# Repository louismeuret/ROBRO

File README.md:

# ROBRO
To install toolchain, use sudo apt install gcc-arm-none-eabi binutils-arm-none-eabi libnewlib-arm-none-eabi
Then in the folder, write make

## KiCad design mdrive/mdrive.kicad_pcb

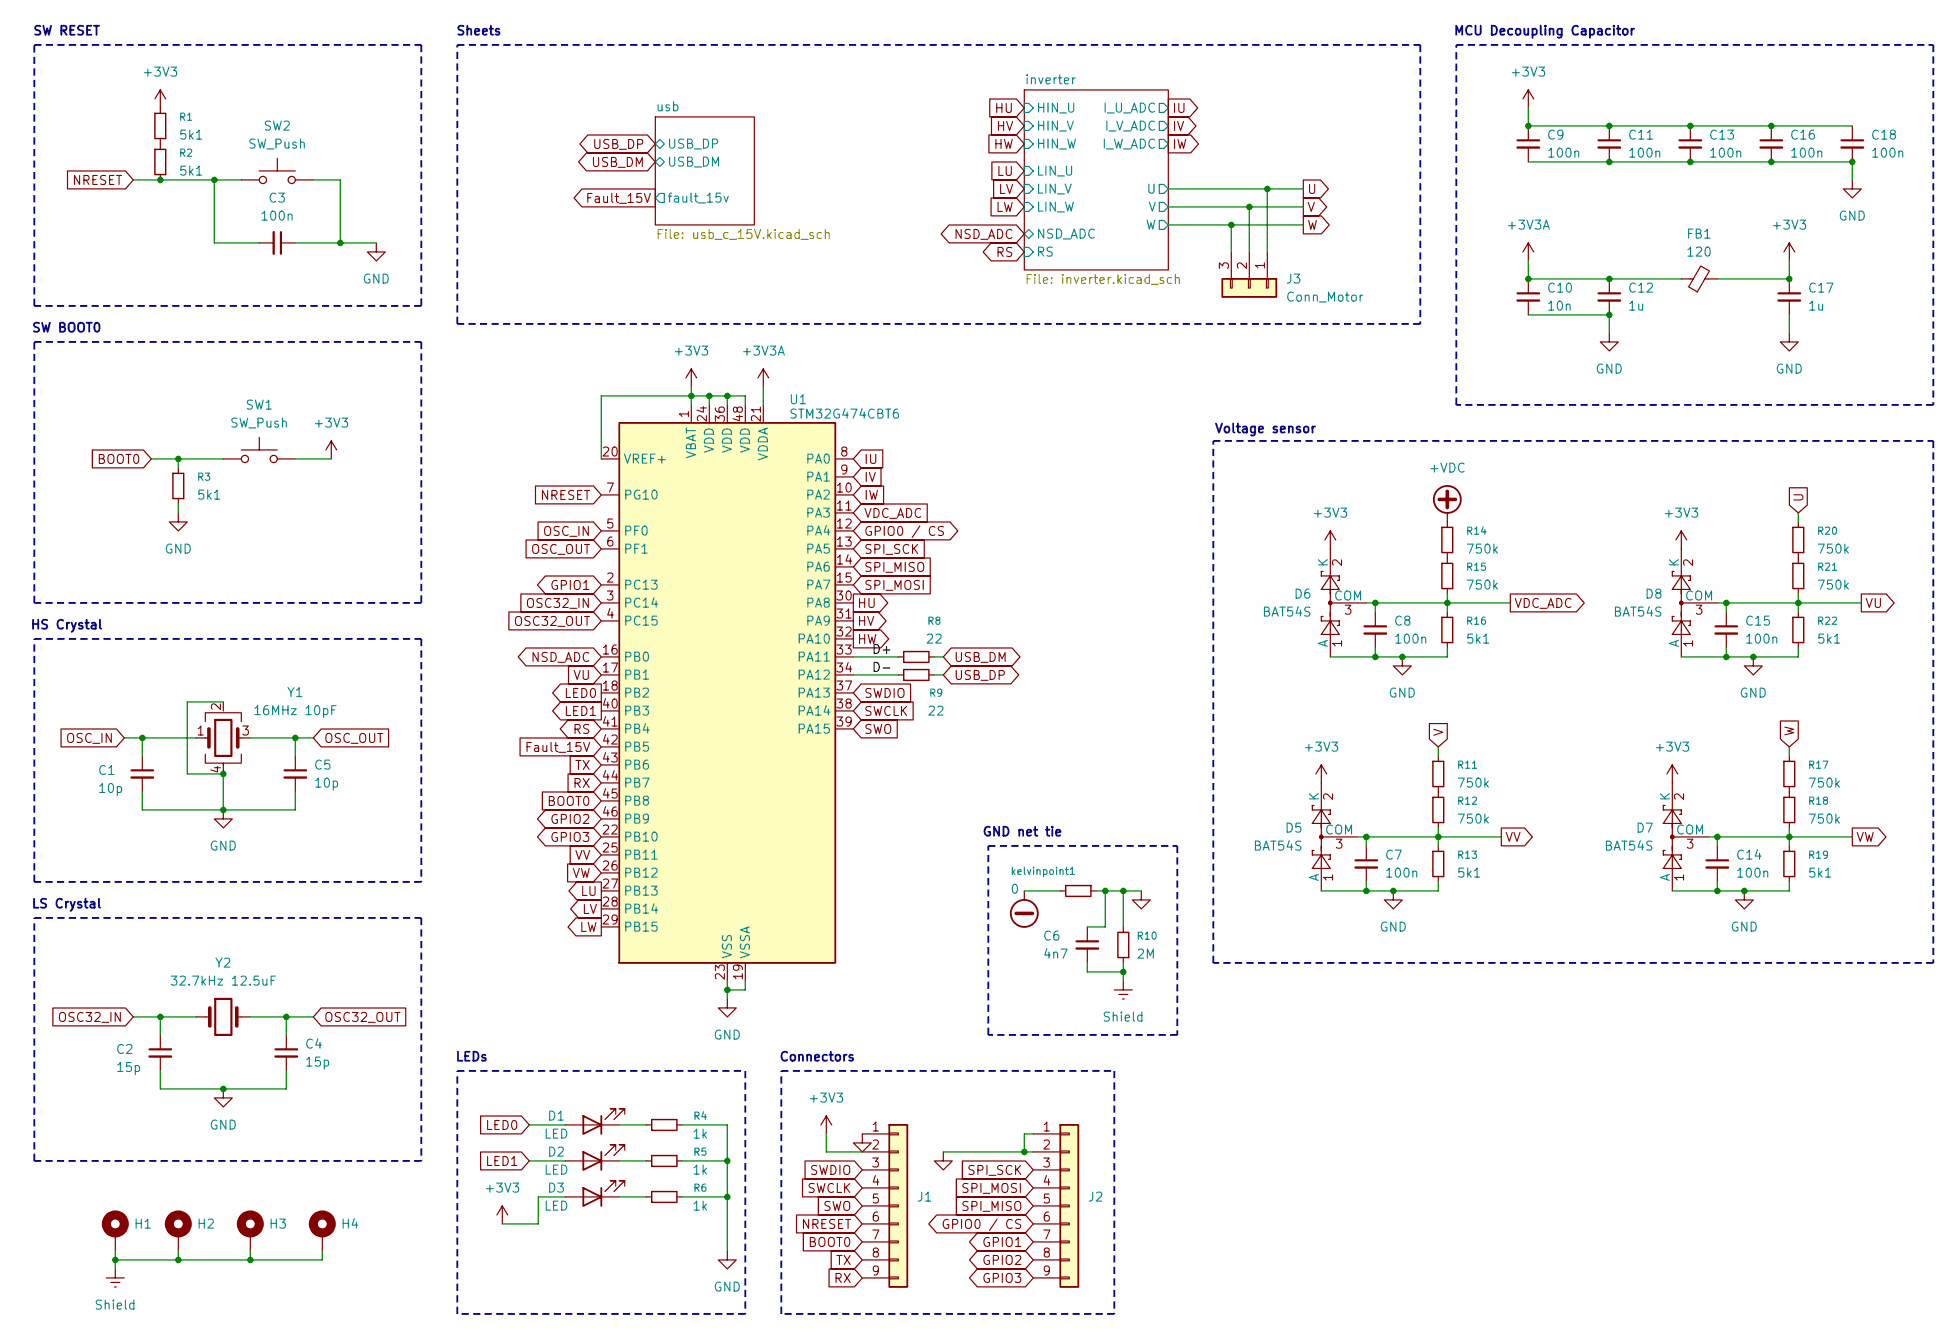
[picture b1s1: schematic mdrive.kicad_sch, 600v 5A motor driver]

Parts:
C1, C5: 10p; C_0603_1608Metric_Pad1.08x0.95mm_HandSolder
C2, C4: 15p; C_0603_1608Metric_Pad1.08x0.95mm_HandSolder
C3, C7, C8, C9, C11, C13, C14, C15, C16, C18: 100n; C_0603_1608Metric_Pad1.08x0.95mm_HandSolder
C6: 4n7; C_0603_1608Metric_Pad1.08x0.95mm_HandSolder
C10: 10n; C_0603_1608Metric_Pad1.08x0.95mm_HandSolder
C12, C17: 1u; C_0603_1608Metric_Pad1.08x0.95mm_HandSolder
D1, D2, D3: LED; LED_0805_2012Metric_Pad1.15x1.40mm_HandSolder
D5, D6, D7, D8: BAT54S; SOT-23
FB1: 120; R_0603_1608Metric_Pad0.98x0.95mm_HandSolder
H1, H2, H3, H4: MountingHole; MountingHole_4.3mm_M4_DIN965_Pad_TopBottom
J1, J2: Conn_01x09; PinHeader_1x09_P2.54mm_Vertical
J3: Conn_Motor; 3POS_3.5_TH
R1, R2, R3: 5k1; R_0603_1608Metric_Pad0.98x0.95mm_HandSolder
R4, R5, R6: 1k; R_0603_1608Metric_Pad0.98x0.95mm_HandSolder
R8, R9: 22; R_0603_1608Metric_Pad0.98x0.95mm_HandSolder
R10: 2M; R_1206_3216Metric_Pad1.30x1.75mm_HandSolder
R11, R12, R14, R15, R17, R18, R20, R21: 750k; R_1206_3216Metric_Pad1.30x1.75mm_HandSolder
R13, R16, R19, R22: 5k1; R_1206_3216Metric_Pad1.30x1.75mm_HandSolder
SW1, SW2: SW_Push; SW_SPST_TL3342
U1: STM32G474CBT6; LQFP-48_7x7mm_P0.5mm
Y1: 16MHz 10pF; Crystal_SMD_3225-4Pin_3.2x2.5mm_HandSoldering
Y2: 32.7kHz 12.5uF; Crystal_SMD_3215-2Pin_3.2x1.5mm
kelvinpoint1: 0; NetTie-2_SMD_Pad2.0mm

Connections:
+3V3: C9.1, C11.1, C13.1, C16.1, C17.1, C18.1, D3.2 (A), D5.2 (K), D6.2 (K), D7.2 (K), D8.2 (K), FB1.2, J1.2, R1.1, SW1.2, U1.1 (VBAT), U1.20 (VREF+), U1.24 (VDD), U1.36 (VDD), U1.48 (VDD); also elsewhere on the board
+3V3A: C10.1, C12.1, FB1.1, U1.21 (VDDA)
-VDC: kelvinpoint1.2; also elsewhere on the board
/D+: R8.1, U1.33 (PA11)
/D-: R9.1, U1.34 (PA12)
BOOT0: J1.7, R3.1, SW1.1, U1.45 (PB8)
Fault_15V: U1.42 (PB5); also elsewhere on the board
GND: C1.2, C2.2, C3.1, C4.2, C5.2, C6.1, C7.2, C8.2, C9.2, C10.2, C11.2, C12.2, C13.2, C14.2, C15.2, C16.2, C17.2, C18.2, D5.1 (A), D6.1 (A), D7.1 (A), D8.1 (A), J1.1, J2.1, J2.2, R3.2, R4.2, R5.2, R6.2, R10.2, R13.2, R16.2, R19.2, R22.2, SW2.2, U1.19 (VSSA), U1.23 (VSS), U1.35 (VSS), U1.47 (VSS), Y1.2 (G), Y1.4 (G), kelvinpoint1.1; also elsewhere on the board
GPIO0 / CS: J2.6, U1.12 (PA4)
GPIO1: J2.7, U1.2 (PC13)
GPIO2: J2.8, U1.46 (PB9)
GPIO3: J2.9, U1.22 (PB10)
HU: U1.30 (PA8); also elsewhere on the board
HV: U1.31 (PA9); also elsewhere on the board
HW: U1.32 (PA10); also elsewhere on the board
IU: U1.8 (PA0); also elsewhere on the board
IV: U1.9 (PA1); also elsewhere on the board
IW: U1.10 (PA2); also elsewhere on the board
LED0: D1.2 (A), U1.18 (PB2); also elsewhere on the board
LED1: D2.2 (A), U1.40 (PB3)
LU: U1.27 (PB13); also elsewhere on the board
LV: U1.28 (PB14); also elsewhere on the board
LW: U1.29 (PB15); also elsewhere on the board
NRESET: C3.2, J1.6, R2.2, SW2.1, U1.7 (PG10)
NSD_ADC: U1.16 (PB0); also elsewhere on the board
unnamed: D1.1 (K), R4.1
unnamed: D2.1 (K), R5.1
unnamed: D3.1 (K), R6.1
unnamed: R1.2, R2.1
unnamed 45: R11.2, R12.1; also elsewhere on the board
unnamed 46: R14.2, R15.1; also elsewhere on the board
unnamed 47: R17.2, R18.1; also elsewhere on the board
unnamed 48: R20.2, R21.1; also elsewhere on the board
OSC32_IN: C2.1, U1.3 (PC14), Y2.1
OSC32_OUT: C4.1, U1.4 (PC15), Y2.2
OSC_IN: C1.1, U1.5 (PF0), Y1.1
OSC_OUT: C5.1, U1.6 (PF1), Y1.3
RS: U1.41 (PB4); also elsewhere on the board
RX: J1.9, U1.44 (PB7)
SPI_MISO: J2.5, U1.14 (PA6)
SPI_MOSI: J2.4, U1.15 (PA7)
SPI_SCK: J2.3, U1.13 (PA5)
SWCLK: J1.4, U1.38 (PA14)
SWDIO: J1.3, U1.37 (PA13)
SWO: J1.5, U1.39 (PA15)
Shield: C6.2, H1.1 (1_1), H2.1 (1_1), H3.1 (1_1), H4.1 (1_1), R10.1; also elsewhere on the board
TX: J1.8, U1.43 (PB6)
U: J3.1, R20.1; also elsewhere on the board
USB_DM: R8.2; also elsewhere on the board
USB_DP: R9.2; also elsewhere on the board
V: J3.2, R11.1; also elsewhere on the board
VDC_ADC: C8.1, D6.3 (COM), R15.2, R16.1, U1.11 (PA3)
VU: C15.1, D8.3 (COM), R21.2, R22.1, U1.17 (PB1)
VV: C7.1, D5.3 (COM), R12.2, R13.1, U1.25 (PB11)
VW: C14.1, D7.3 (COM), R18.2, R19.1, U1.26 (PB12); also elsewhere on the board
W: J3.3, R17.1; also elsewhere on the board

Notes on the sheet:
MCU Decoupling Capacitor
GND net tie
Connectors
Voltage sensor
LS Crystal
Sheets
LEDs
SW BOOT0
SW RESET
HS Crystal

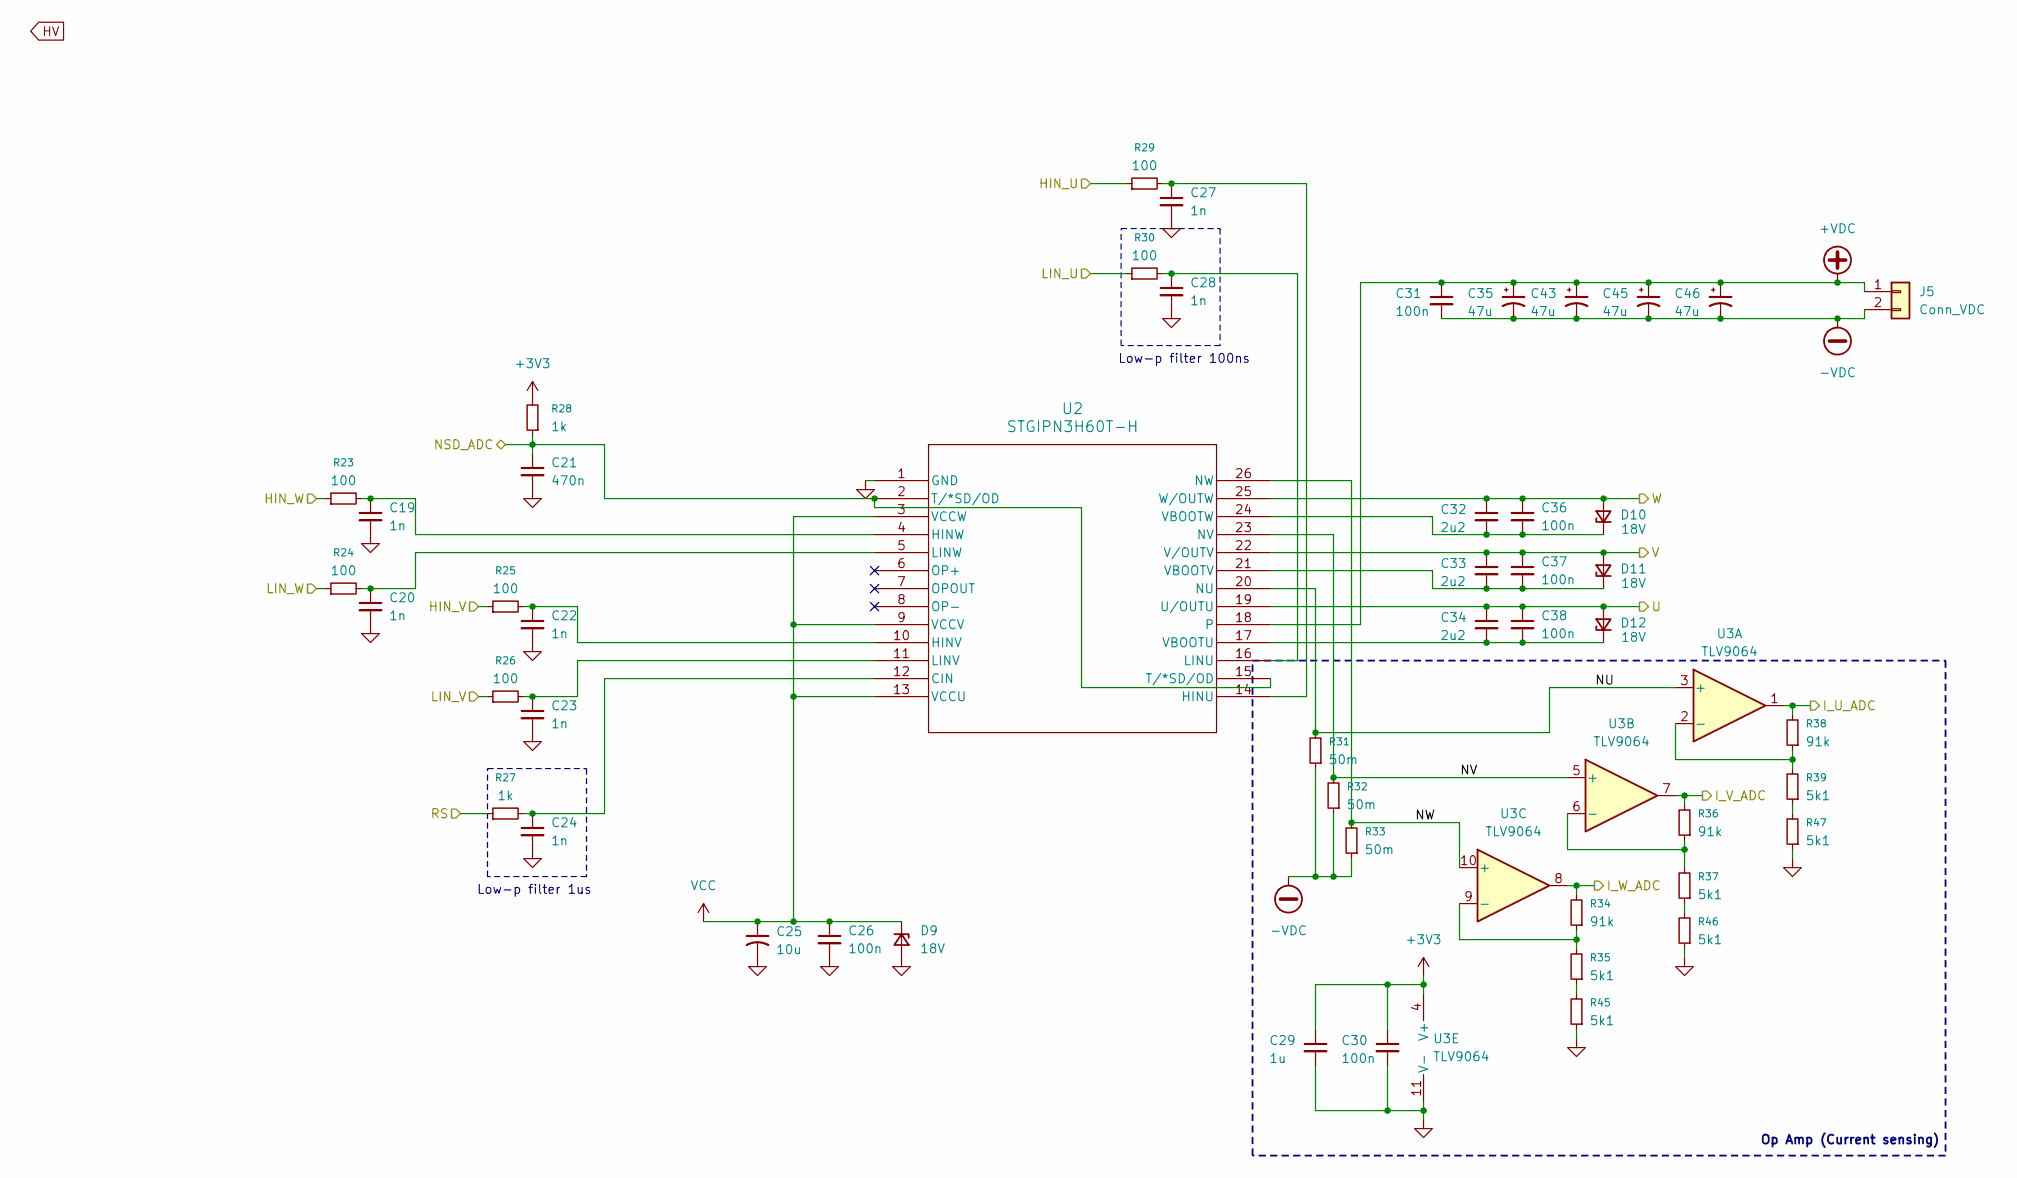
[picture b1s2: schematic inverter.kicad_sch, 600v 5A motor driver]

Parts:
C19, C20, C22, C23, C24, C27, C28: 1n; C_0603_1608Metric_Pad1.08x0.95mm_HandSolder
C21: 470n; C_0603_1608Metric_Pad1.08x0.95mm_HandSolder
C25: 10u; C_0603_1608Metric_Pad1.08x0.95mm_HandSolder
C26, C30: 100n; C_0603_1608Metric_Pad1.08x0.95mm_HandSolder
C29: 1u; C_0603_1608Metric_Pad1.08x0.95mm_HandSolder
C31, C36, C37, C38: 100n; C_1206_3216Metric_Pad1.33x1.80mm_HandSolder
C32, C33, C34: 2u2; C_1206_3216Metric_Pad1.33x1.80mm_HandSolder
C35, C43, C45, C46: 47u; CP_Radial_D10.0mm_P5.00mm
D9, D10, D11, D12: 18V; D_SOD-123
J5: Conn_VDC; DB301V-3.5-2P-GN-S
R23, R24, R25, R26, R29, R30: 100; R_0603_1608Metric_Pad0.98x0.95mm_HandSolder
R27, R28: 1k; R_0603_1608Metric_Pad0.98x0.95mm_HandSolder
R31, R32, R33: 50m; R_1206_3216Metric_Pad1.30x1.75mm_HandSolder
R34, R36, R38: 91k; R_0603_1608Metric_Pad0.98x0.95mm_HandSolder
R35, R37, R39, R45, R46, R47: 5k1; R_0603_1608Metric_Pad0.98x0.95mm_HandSolder
U2: STGIPN3H60T-H; NDIP-26_12P55X29P25_STM
U3: TLV9064; SOIC-14_3.9x8.7mm_P1.27mm

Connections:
+3V3: C29.1, C30.1, R28.2, U3.4 (V+); also elsewhere on the board
+VDC: C31.1, C35.1, C43.1, C45.1, C46.1, J5.1, U2.18; also elsewhere on the board
-VDC: C31.2, C35.2, C43.2, C45.2, C46.2, J5.2, R31.1, R32.1, R33.1; also elsewhere on the board
/inverter/NU: R31.2, U2.20 (NU), U3.3 (+)
/inverter/NV: R32.2, U2.23 (NV), U3.5 (+)
/inverter/NW: R33.2, U2.26 (NW), U3.10 (+)
GND: C19.2, C20.2, C21.2, C22.2, C23.2, C24.2, C25.2, C26.2, C27.2, C28.2, C29.2, C30.2, D9.2 (A), R45.1, R46.1, R47.1, U2.1 (GND), U3.11 (V-); also elsewhere on the board
HU: R29.1; also elsewhere on the board
HV: R25.1; also elsewhere on the board
HW: R23.1; also elsewhere on the board
IU: R38.2, U3.1; also elsewhere on the board
IV: R36.2, U3.7; also elsewhere on the board
IW: R34.2, U3.8; also elsewhere on the board
LV: R26.1; also elsewhere on the board
LW: R24.1; also elsewhere on the board
NSD_ADC: C21.1, R28.1, U2.2 (T/*SD/OD), U2.15 (T/*SD/OD); also elsewhere on the board
unnamed: C32.2, C36.2, D10.1 (K), U2.24 (VBOOTW)
unnamed: C33.2, C37.2, D11.1 (K), U2.21 (VBOOTV)
unnamed: C34.2, C38.2, D12.1 (K), U2.17 (VBOOTU)
unnamed: R35.1, R45.2
unnamed: R37.1, R46.2
unnamed: R39.1, R47.2
unnamed: C24.1, R27.2, U2.12 (CIN)
unnamed: C27.1, R29.2, U2.14 (HINU)
unnamed: C22.1, R25.2, U2.10 (HINV)
unnamed: C19.1, R23.2, U2.4 (HINW)
unnamed 56: C28.1, R30.2, U2.16 (LINU); also elsewhere on the board
unnamed: C23.1, R26.2, U2.11 (LINV)
unnamed: C20.1, R24.2, U2.5 (LINW)
unnamed: R38.1, R39.2, U3.2 (-)
unnamed: R36.1, R37.2, U3.6 (-)
unnamed: R34.1, R35.2, U3.9 (-)
RS: R27.1; also elsewhere on the board
U: C34.1, C38.1, D12.2 (A), U2.19 (U/OUTU); also elsewhere on the board
V: C33.1, C37.1, D11.2 (A), U2.22 (V/OUTV); also elsewhere on the board
VCC: C25.1, C26.1, D9.1 (K), U2.3 (VCCW), U2.9 (VCCV), U2.13 (VCCU); also elsewhere on the board
W: C32.1, C36.1, D10.2 (A), U2.25 (W/OUTW); also elsewhere on the board

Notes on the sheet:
Low-p filter 100ns
Op Amp (Current sensing)
Low-p filter 1us

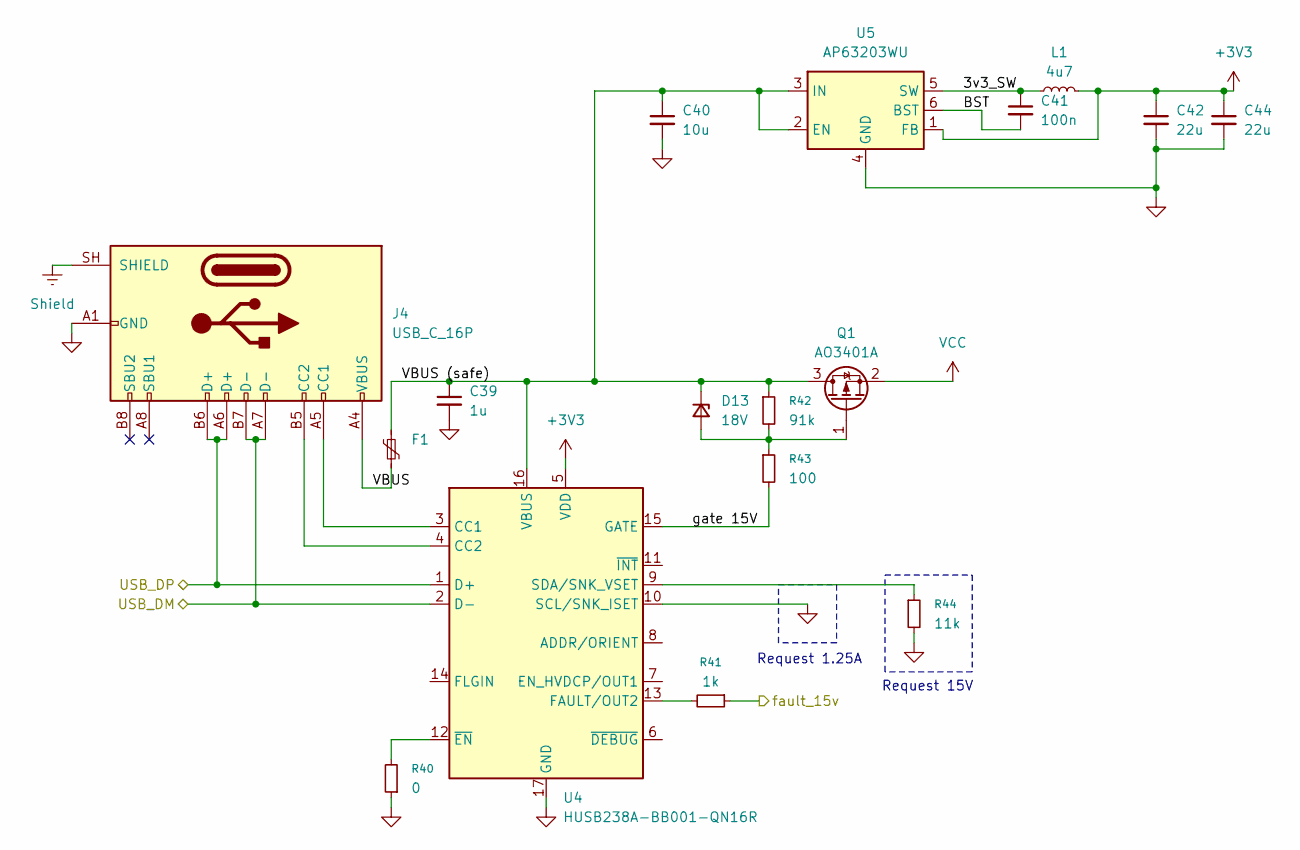
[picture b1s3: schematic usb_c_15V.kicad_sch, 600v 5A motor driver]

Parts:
C39: 1u; C_0603_1608Metric_Pad1.08x0.95mm_HandSolder
C40: 10u; C_0603_1608Metric_Pad1.08x0.95mm_HandSolder
C41: 100n; C_0603_1608Metric_Pad1.08x0.95mm_HandSolder
C42, C44: 22u; C_0603_1608Metric_Pad1.08x0.95mm_HandSolder
D13: 18V; D_SOD-123
F1: Polyfuse_Small; Fuse_1812_4532Metric_Pad1.30x3.40mm_HandSolder
J4: USB_C_16P; USB_C_Receptacle_HRO_TYPE-C-31-M-12
L1: 4u7; L_Changjiang_FXL0530
Q1: AO3401A; SOT-23
R40: 0; R_0201_0603Metric_Pad0.64x0.40mm_HandSolder
R41: 1k; R_0603_1608Metric_Pad0.98x0.95mm_HandSolder
R42: 91k; R_0603_1608Metric_Pad0.98x0.95mm_HandSolder
R43: 100; R_0603_1608Metric_Pad0.98x0.95mm_HandSolder
R44: 11k; R_0603_1608Metric_Pad0.98x0.95mm_HandSolder
U4: HUSB238A-BB001-QN16R; WQFN-16-1EP_3x3mm_P0.5mm_EP1.75x1.75mm
U5: AP63203WU; TSOT-23-6

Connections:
+3V3: C42.1, C44.1, L1.2, U4.5 (VDD), U5.1 (FB); also elsewhere on the board
/usb/3v3_SW: C41.1, L1.1, U5.5 (SW)
/usb/BST: C41.2, U5.6 (BST)
/usb/VBUS: F1.2, J4.A4 (VBUS), J4.A9 (VBUS), J4.B4 (VBUS), J4.B9 (VBUS)
/usb/VBUS (safe): C39.1, C40.1, D13.1 (K), F1.1, Q1.3 (D), R42.1, U4.16 (VBUS), U5.2 (EN), U5.3 (IN)
/usb/gate 15V: R43.2, U4.15 (GATE)
Fault_15V: R41.1; also elsewhere on the board
GND: C39.2, C40.2, C42.2, C44.2, J4.A1 (GND), J4.A12 (GND), J4.B1 (GND), J4.B12 (GND), R40.1, R44.2, U4.10 (SCL/SNK_ISET), U4.17 (GND), U5.4 (GND); also elsewhere on the board
unnamed: D13.2 (A), Q1.1 (G), R42.2, R43.1
unnamed: J4.A5 (CC1), U4.3 (CC1)
unnamed: J4.B5 (CC2), U4.4 (CC2)
unnamed: R41.2, U4.13 (FAULT/OUT2)
unnamed: R44.1, U4.9 (SDA/SNK_VSET)
unnamed: R40.2, U4.12 (~EN)
Shield: J4.SH (SHIELD); also elsewhere on the board
USB_DM: J4.A7 (D-), J4.B7 (D-), U4.2 (D-); also elsewhere on the board
USB_DP: J4.A6 (D+), J4.B6 (D+), U4.1 (D+); also elsewhere on the board
VCC: Q1.2 (S); also elsewhere on the board

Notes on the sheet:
Request 15V
Request 1.25A

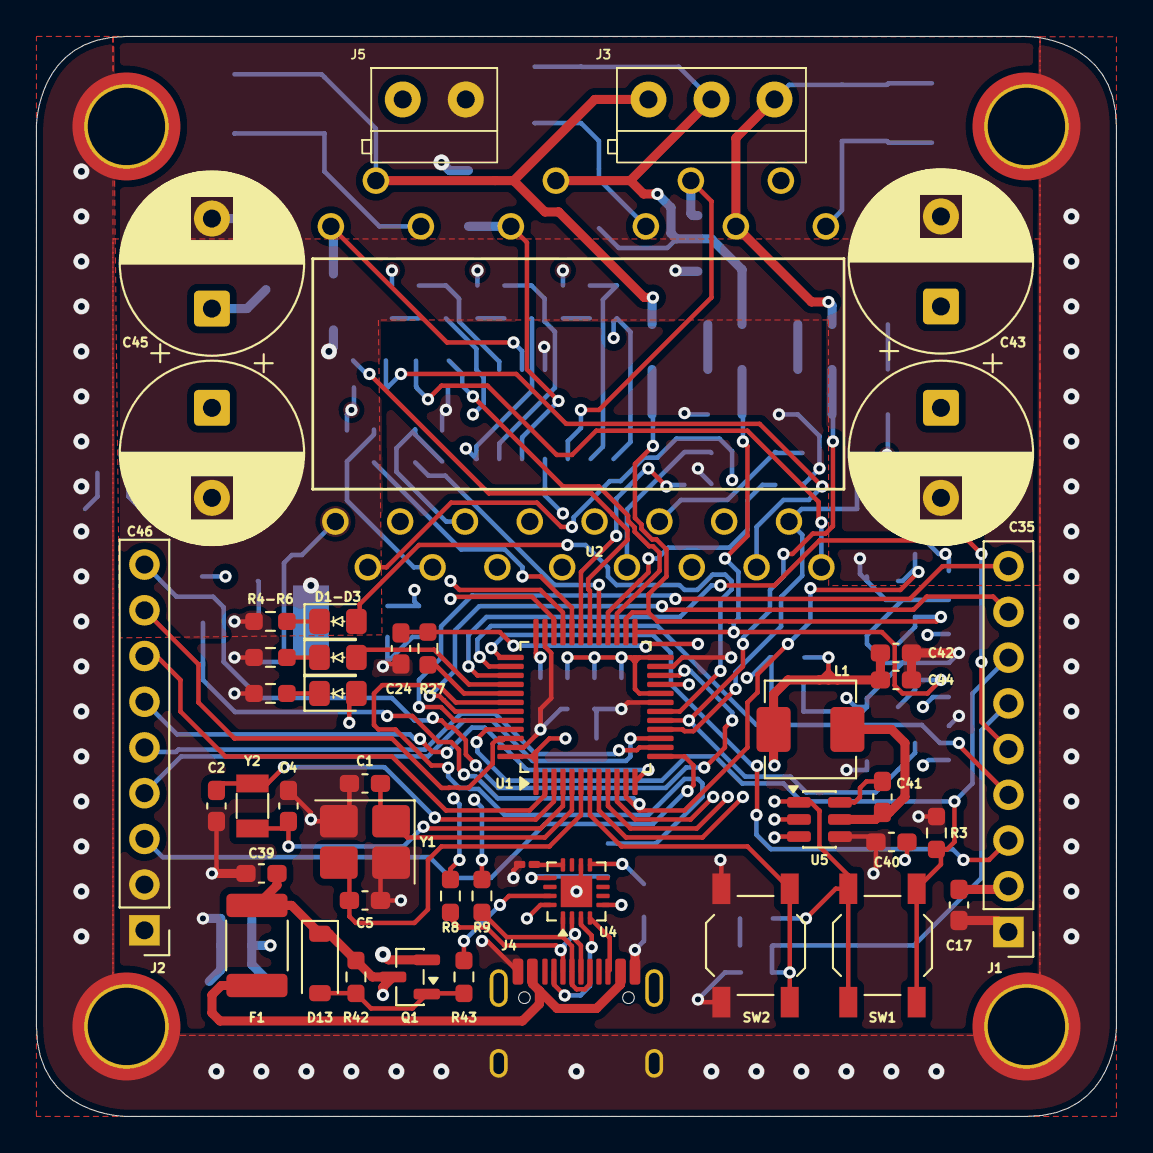
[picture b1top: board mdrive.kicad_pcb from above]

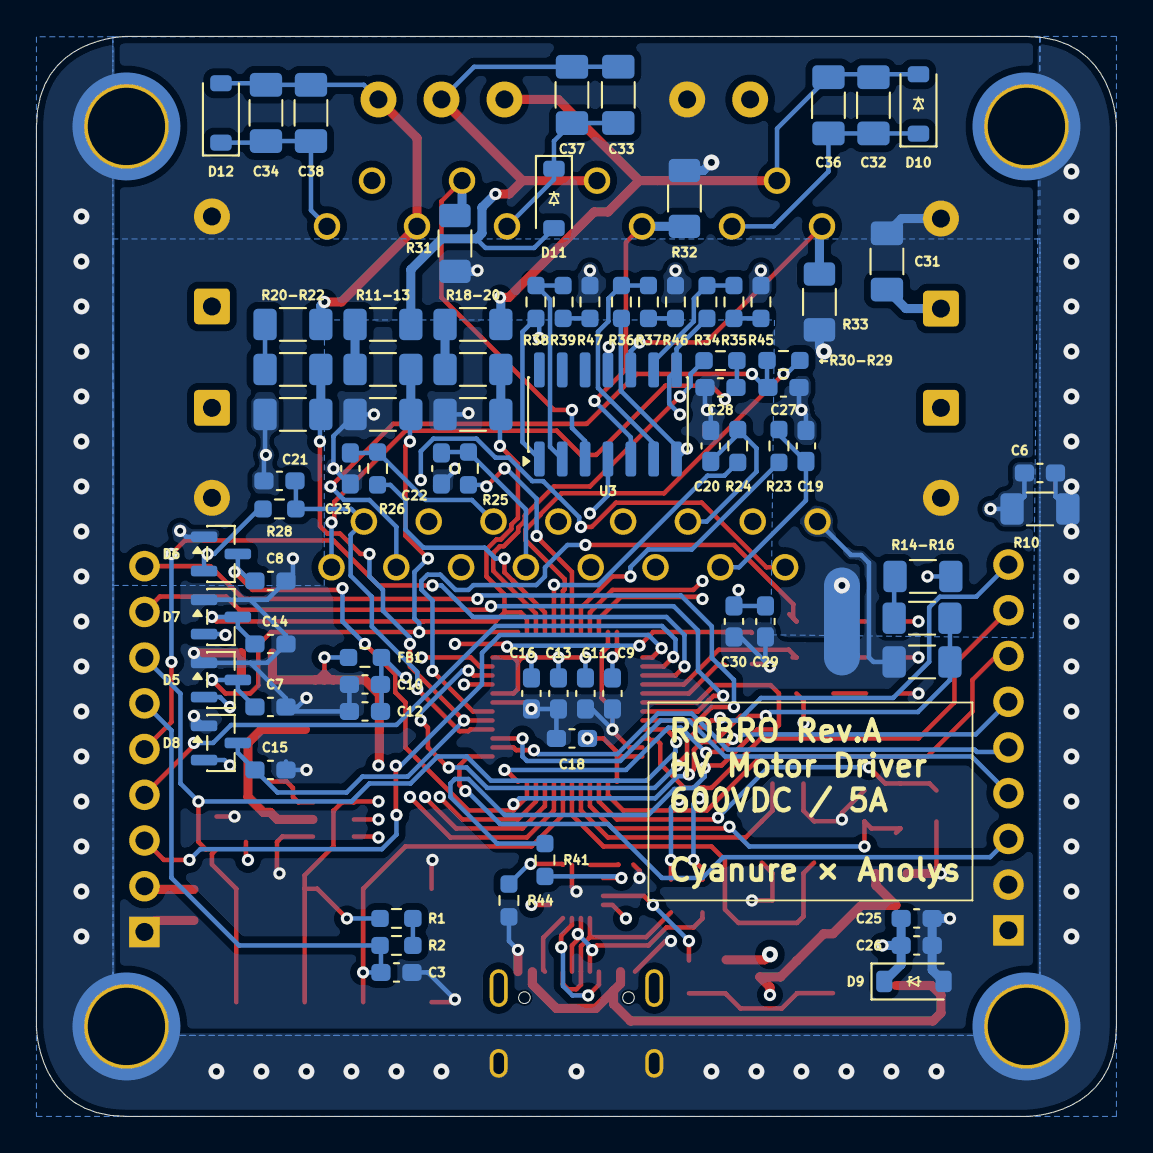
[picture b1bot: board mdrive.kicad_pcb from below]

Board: 4 copper layers, 60.0 x 60.0 mm, 127 parts (78 on the bottom side), 88 nets.

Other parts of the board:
D1-D3: LED; LED_0805_2012Metric_Pad1.15x1.40mm_HandSolder
R4-R6: 1k; R_0603_1608Metric_Pad0.98x0.95mm_HandSolder
R11-13, R14-R16, R18-20, R20-R22: 750k; R_1206_3216Metric_Pad1.30x1.75mm_HandSolder
←R30-R29: 100; R_0603_1608Metric_Pad0.98x0.95mm_HandSolder

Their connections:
+VDC: R14-R16.1; also elsewhere on the board
GND: R4-R6.2; also elsewhere on the board
LED0: D1-D3.2 (A); also elsewhere on the board
LU: ←R30-R29.1; also elsewhere on the board
unnamed: D1-D3.1 (K), R4-R6.1
unnamed 45: R11-13.2; also elsewhere on the board
unnamed 46: R14-R16.2; also elsewhere on the board
unnamed 47: R18-20.1; also elsewhere on the board
unnamed 48: R20-R22.2; also elsewhere on the board
unnamed 56: ←R30-R29.2; also elsewhere on the board
U: R20-R22.1; also elsewhere on the board
V: R11-13.1; also elsewhere on the board
VW: R18-20.2; also elsewhere on the board

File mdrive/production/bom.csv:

Designator,Footprint,Quantity,Value,LCSC Part #
"C1, C5",0603,2,10p,
C10,0603,1,10n,
"C11, C13, C14, C15, C16, C18, C26, C3, C30, C41, C7, C8, C9",0603,13,100n,
"C12, C17, C29, C39",0603,4,1u,
"C19, C20, C22, C23, C24, C27, C28",0603,7,1n,
"C2, C4",0603,2,15p,
C21,0603,1,470n,
"C25, C40",0603,2,10u,
"C31, C36, C37, C38",1206,4,100n,
"C32, C33, C34",1206,3,2u2,
"C35, C43, C45, C46",CP_Radial_D10.0mm_P5.00mm,4,47u,
"C42, C44",0603,2,22u,
C6,0603,1,4n7,
"D1-D3, D2, D3",0805,3,LED,
"D10, D11, D12, D13, D9",D_SOD-123,5,18V,
"D5, D6, D7, D8",SOT-23,4,BAT54S,
F1,1812,1,Polyfuse_Small,
FB1,0603,1,120,
"J1, J2",PinHeader_1x09_P2.54mm_Vertical,2,Conn_01x09,
J3,3POS_3.5_TH,1,Conn_Motor,
J4,USB_C_Receptacle_HRO_TYPE-C-31-M-12,1,USB_C_16P,
J5,DB301V-3.5-2P-GN-S,1,Conn_VDC,
KELVINPOINT1,NetTie-2_SMD_Pad2.0mm,1,0,
L1,L_Changjiang_FXL0530,1,4u7,
Q1,SOT-23,1,AO3401A,
"R1, R2, R3, R35, R37, R39, R45, R46, R47",0603,9,5k1,
R10,1206,1,2M,
"R11-13, R12, R14-R16, R15, R17, R18-20, R20-R22, R21",1206,8,750k,
"R13, R16, R19, R22",1206,4,5k1,
"R23, R24, R25, R26, R29, R43, ←R30-R29",0603,7,100,
"R27, R28, R4-R6, R41, R5, R6",0603,6,1k,
"R31, R32, R33",1206,3,50m,
"R34, R36, R38, R42",0603,4,91k,
R40,0201,1,0,
R44,0603,1,11k,
"R8, R9",0603,2,22,
"SW1, SW2",SW_SPST_TL3342,2,SW_Push,
U1,LQFP-48_7x7mm_P0.5mm,1,STM32G474CBT6,
U2,NDIP-26_12P55X29P25_STM,1,STGIPN3H60T-H,
U3,SOIC-14_3.9x8.7mm_P1.27mm,1,TLV9064,
U4,WQFN-16-1EP_3x3mm_P0.5mm_EP1.75x1.75mm,1,HUSB238A-BB001-QN16R,
U5,TSOT-23-6,1,AP63203WU,
Y1,Crystal_SMD_3225-4Pin_3.2x2.5mm_HandSoldering,1,16MHz 10pF,
Y2,Crystal_SMD_3215-2Pin_3.2x1.5mm,1,32.7kHz 12.5uF,

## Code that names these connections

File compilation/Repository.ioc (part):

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Mcu.Name=STM32G474C(B-C-E)Tx
Mcu.Package=LQFP48
Mcu.UserName=STM32G474CBTx
PA0.Mode=IN1-Single-Ended
PA0.Signal=ADC1_IN1
PA1.Mode=IN2-Single-Ended
PA1.Signal=ADC1_IN2
PA10.Signal=S_TIM1_CH3
PA11.Mode=Device
PA11.Signal=USB_DM
PA12.Mode=Device
PA12.Signal=USB_DP
PA13.Signal=SYS_JTMS-SWDIO
PA14.Signal=SYS_JTCK-SWCLK
PA15.Signal=GPIO_Output
PA2.Mode=IN3-Single-Ended
PA2.Signal=ADC1_IN3
PA3.Mode=IN4-Single-Ended
PA3.Signal=ADC1_IN4
PA4.Signal=GPIO_Output
PA5.Mode=Full_Duplex_Master
PA5.Signal=SPI1_SCK
PA6.Mode=Full_Duplex_Master
PA6.Signal=SPI1_MISO
PA7.Mode=Full_Duplex_Master
PA7.Signal=SPI1_MOSI
PA8.Signal=S_TIM1_CH1
PA9.Signal=S_TIM1_CH2
PB0.Mode=IN15-Single-Ended
PB0.Signal=ADC1_IN15
PB1.Mode=IN12-Single-Ended
PB1.Signal=ADC1_IN12
PB10.Signal=GPXTI10
PB11.Mode=IN14-Single-Ended
PB11.Signal=ADC1_IN14
PB12.Mode=IN11-Single-Ended
PB12.Signal=ADC1_IN11
PB13.Mode=PWM Generation1 CH1 CH1N
PB13.Signal=TIM1_CH1N
PB14.Mode=PWM Generation2 CH2 CH2N
PB14.Signal=TIM1_CH2N
PB15.Mode=PWM Generation3 CH3 CH3N
PB15.Signal=TIM1_CH3N
PB2.Signal=GPIO_Output
PB3.Signal=GPIO_Output
PB4.Signal=GPIO_Output
PB5.Signal=GPIO_Input
PB6.Mode=Asynchronous
PB6.Signal=USART1_TX
PB7.Mode=Asynchronous
PB7.Signal=USART1_RX
PB9.Signal=GPIO_Output
PC13.Signal=GPIO_Output
PC14-OSC32_IN.Mode=LSE-External-Oscillator
PC14-OSC32_IN.Signal=RCC_OSC32_IN
PC15-OSC32_OUT.Mode=LSE-External-Oscillator
PC15-OSC32_OUT.Signal=RCC_OSC32_OUT
PF0-OSC_IN.Mode=HSE-External-Oscillator
PF0-OSC_IN.Signal=RCC_OSC_IN
PF1-OSC_OUT.Mode=HSE-External-Oscillator
PF1-OSC_OUT.Signal=RCC_OSC_OUT
RCC.HSE_VALUE=16000000
RCC.SYSCLKFreq_VALUE=16000000
board=custom

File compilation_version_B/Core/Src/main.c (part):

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 * All four signals land on the board's existing header, so nothing has to be
 * soldered to the LED pads:
 *
 *   PB3 (GPIO4, SPI_SCK)  -> ESP32 SCLK
 *   PA7 (GPIO6, SPI_MOSI) -> ESP32 MOSI   (telemetry out)
 *   PB4 (GPIO5, SPI_MISO) <- ESP32 MISO   (commands in)
 *   PB9 (free header pin) -> ESP32 CS     (software NSS, active low)
 *   GND                   -- GND
 *
 * SPI was chosen because it is the only full-duplex link available on the
 * reachable pins: PB3/PB4/PA14 all map to USART2, which is already driving the
 * RS485 daisy chain, and PB9's UART partner (USART3_RX) is PB8-BOOT0.
 *
 * SPI1 was already configured by CubeMX as a full-duplex master with soft NSS
 * and never used. Two changes are needed: 8-bit words instead of 4, and a
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#define ESP_LED_AUTO             0u
#define ESP_LED_ON               1u
#define ESP_LED_OFF              2u
#define ESP_LED_COUNT            2u     /* 0 = LED1 (PB6), 1 = LED2 (PB7) */

#define ESP_CS_PORT              GPIOB
#define ESP_CS_PIN               GPIO_PIN_9
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PCD_HandleTypeDef hpcd_USB_FS;

/* USER CODE BEGIN PV */
static volatile uint8_t fault_15v = 0;       /* PA15: 1 = no 15V rail */
static volatile uint32_t dc_peer_frames = 0; /* valid frames seen from other boards */
/* USER CODE END PV */

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  MX_USART2_UART_Init();
  /* USER CODE BEGIN 2 */
  /* Sinusoidal open-loop drive through the STGIPN3H60T IPM.
   *   PA8/PB13  = HIN1/LIN1 -> phase U
   *   PA9/PB14  = HIN2/LIN2 -> phase V
   *   PA10/PB15 = HIN3/LIN3 -> phase W
   * TIM1 produces the complementary HIN/LIN pairs with dead-time; the IPM
   * inputs are active-high. Motor_PWM_Update() (called from the TIM1 update
   * interrupt) drives each phase with a 120-degree-shifted sine, ramping
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   * the previous equal-duty smoke test which produced zero line-to-line
   * voltage and no torque. */

  /* Hold PA5 (NSD_ADC) high at all times to keep the current/voltage-sense
   * signal conditioning out of shutdown. It defaults to a plain input;
   * override it to a push-pull output and drive it high. Set ODR high first
   * to avoid a glitch when the pin switches to output. */
  HAL_GPIO_WritePin(GPIOA, GPIO_PIN_5, GPIO_PIN_SET);
  {
    GPIO_InitTypeDef pa5 = {0};
    pa5.Pin   = GPIO_PIN_5;
    pa5.Mode  = GPIO_MODE_OUTPUT_PP;
    pa5.Pull  = GPIO_NOPULL;
    pa5.Speed = GPIO_SPEED_FREQ_LOW;
    HAL_GPIO_Init(GPIOA, &pa5);
  }

  /* PB11 ("RS") is NOT a digital IPM enable pin: it feeds an RC filter
   * (R12/C16) into the IPM's CIN pin, the analog overcurrent-comparator
   * input that gates the U-channel driver specifically. Driving it high
   * holds CIN above its trip threshold, permanently faulting out U while
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   * RJ45 jacks). */
  DaisyChain_Init();

  /* ESP32 telemetry/command link on SPI1 (PB3/PB4/PA7 + PB9 as CS). Also
   * calibrates ADC1 and ADC2 -- they were initialised by CubeMX but never
   * calibrated or started. */
  Esp_Init();
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
    /* USER CODE BEGIN 3 */
    /* 15V-supply status housekeeping (preserved from the smoke test).
     * PA15 (Fault_15V) high -> no 15V. The state is also published in the
     * telemetry frame so the ESP32 dashboard can show it. */
    fault_15v = (HAL_GPIO_ReadPin(GPIOA, GPIO_PIN_15) == GPIO_PIN_SET) ? 1u : 0u;
    HAL_GPIO_WritePin(GPIOB, GPIO_PIN_5, fault_15v ? GPIO_PIN_SET : GPIO_PIN_RESET);
    Leds_Apply();

    /* U/V/W duty is updated from the TIM1 update interrupt (Motor_PWM_Update) —
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  HAL_GPIO_WritePin(GPIOB, GPIO_PIN_2|GPIO_PIN_11|GPIO_PIN_5|GPIO_PIN_6
                          |GPIO_PIN_7|GPIO_PIN_9, GPIO_PIN_RESET);

  /*Configure GPIO pin : PC13 */
  GPIO_InitStruct.Pin = GPIO_PIN_13;
  GPIO_InitStruct.Mode = GPIO_MODE_OUTPUT_PP;
  GPIO_InitStruct.Pull = GPIO_NOPULL;
  GPIO_InitStruct.Speed = GPIO_SPEED_FREQ_LOW;
  HAL_GPIO_Init(GPIOC, &GPIO_InitStruct);

  /*Configure GPIO pins : PA5 PA15 */
  GPIO_InitStruct.Pin = GPIO_PIN_5|GPIO_PIN_15;
  GPIO_InitStruct.Mode = GPIO_MODE_INPUT;
  GPIO_InitStruct.Pull = GPIO_NOPULL;
  HAL_GPIO_Init(GPIOA, &GPIO_InitStruct);

  /*Configure GPIO pins : PB2 PB11 PB5 PB6
                           PB7 PB9
    PB9 doubles as the software-NSS chip select for the ESP32 SPI link; it is
    driven high (idle) in Esp_Init(). */
  GPIO_InitStruct.Pin = GPIO_PIN_2|GPIO_PIN_11|GPIO_PIN_5|GPIO_PIN_6
                          |GPIO_PIN_7|GPIO_PIN_9;
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  GPIO_InitStruct.Speed = GPIO_SPEED_FREQ_LOW;
  HAL_GPIO_Init(GPIOB, &GPIO_InitStruct);

  /*Configure GPIO pin : PB10 */
  GPIO_InitStruct.Pin = GPIO_PIN_10;
  GPIO_InitStruct.Mode = GPIO_MODE_IT_RISING;
  GPIO_InitStruct.Pull = GPIO_NOPULL;
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static volatile uint16_t motor_ramp_ms  = (uint16_t)(RAMP_TIME_S * 1000.0f);
static volatile uint8_t motor_reverse   = 0;  /* 1 = swap V/W -> reverse rotation */

/* LED override state. Index 0 = LED1 (PB6), 1 = LED2 (PB7). While a LED is in
 * ESP_LED_AUTO the firmware drives it as before; otherwise the dashboard owns
 * it and the automatic logic leaves it alone. */
static volatile uint8_t led_mode[ESP_LED_COUNT] = { ESP_LED_AUTO, ESP_LED_AUTO };
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  __HAL_TIM_SET_COMPARE(&htim1, TIM_CHANNEL_3, ccw);
}

/* LED1 (PB6) normally mirrors "15V present"; LED2 (PB7) is blinked by the
 * daisy chain. Either can be taken over from the dashboard. */
static void Leds_Apply(void)
{
  if (led_mode[0] == ESP_LED_AUTO)
  {
    HAL_GPIO_WritePin(GPIOB, GPIO_PIN_6, fault_15v ? GPIO_PIN_RESET : GPIO_PIN_SET);
  }
  else
  {
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  }
}

/* ===== ESP32 telemetry / command link (SPI1 master, PB3/PB4/PA7 + PB9 CS) ==
 *
 * One fixed-length full-duplex transfer per period: the telemetry frame is
 * clocked out on MOSI while the ESP32's command frame arrives on MISO. The
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 *    2-3   VDC        4-5   VU        6-7   VV (always 0)
 *    8-9   VW        10-11  IU       12-13  IV       14-15  IW
 *    16    flags: bit0 = 15V fault, bit1 = outputs enabled,
 *                 bit2 = reverse, bit3 = PB10 input level
 *    17    number of daisy-chain peers in the table
 *    18-21 total RS485 frames seen from other boards
 *    22-23 electrical frequency setpoint, centi-Hz
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static void Esp_BuildTelemetry(void)
{
  /* Channel map comes from Repository.ioc:
   *   VDC PB12 ADC1_IN11 | VU PB1 ADC1_IN12 | VW PA6 ADC2_IN3
   *   IU  PA0  ADC1_IN1  | IV PA4 ADC2_IN17 | IW PB0 ADC1_IN15
   * VV has no ADC channel: PB2 is configured as a GPIO output in both .ioc
   * files, so the README's "VV = PB2 = ADC2_IN12" was never true for this
   * pinout. It is sent as 0. To get a real VV, reassign PB2 to ADC2_IN12 in
   * CubeMX and read ADC_CHANNEL_12 on hadc2 here. */
  uint16_t vdc = ADC_ReadChannel(&hadc1, ADC_CHANNEL_11);
  uint16_t vu  = ADC_ReadChannel(&hadc1, ADC_CHANNEL_12);
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{
  Esp_BuildTelemetry();

  /* Software NSS: frame the transfer with PB9. The ESP32's SPI slave uses the
   * CS edges to delimit the transaction, so it must fall before the first
   * clock and rise after the last. */
  HAL_GPIO_WritePin(ESP_CS_PORT, ESP_CS_PIN, GPIO_PIN_RESET);
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    Error_Handler();
  }

  /* CS idles high. MX_GPIO_Init() already made PB9 a push-pull output. */
  HAL_GPIO_WritePin(ESP_CS_PORT, ESP_CS_PIN, GPIO_PIN_SET);

  esp_next_tick = HAL_GetTick() + ESP_PERIOD_MS;
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
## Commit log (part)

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2026-06-12 Working code for the stm32

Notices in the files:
compilation_version_B/Core/Src/main.c:
Copyright (c) 2026 STMicroelectronics.
All rights reserved.
This software is licensed under terms that can be found in the LICENSE file
